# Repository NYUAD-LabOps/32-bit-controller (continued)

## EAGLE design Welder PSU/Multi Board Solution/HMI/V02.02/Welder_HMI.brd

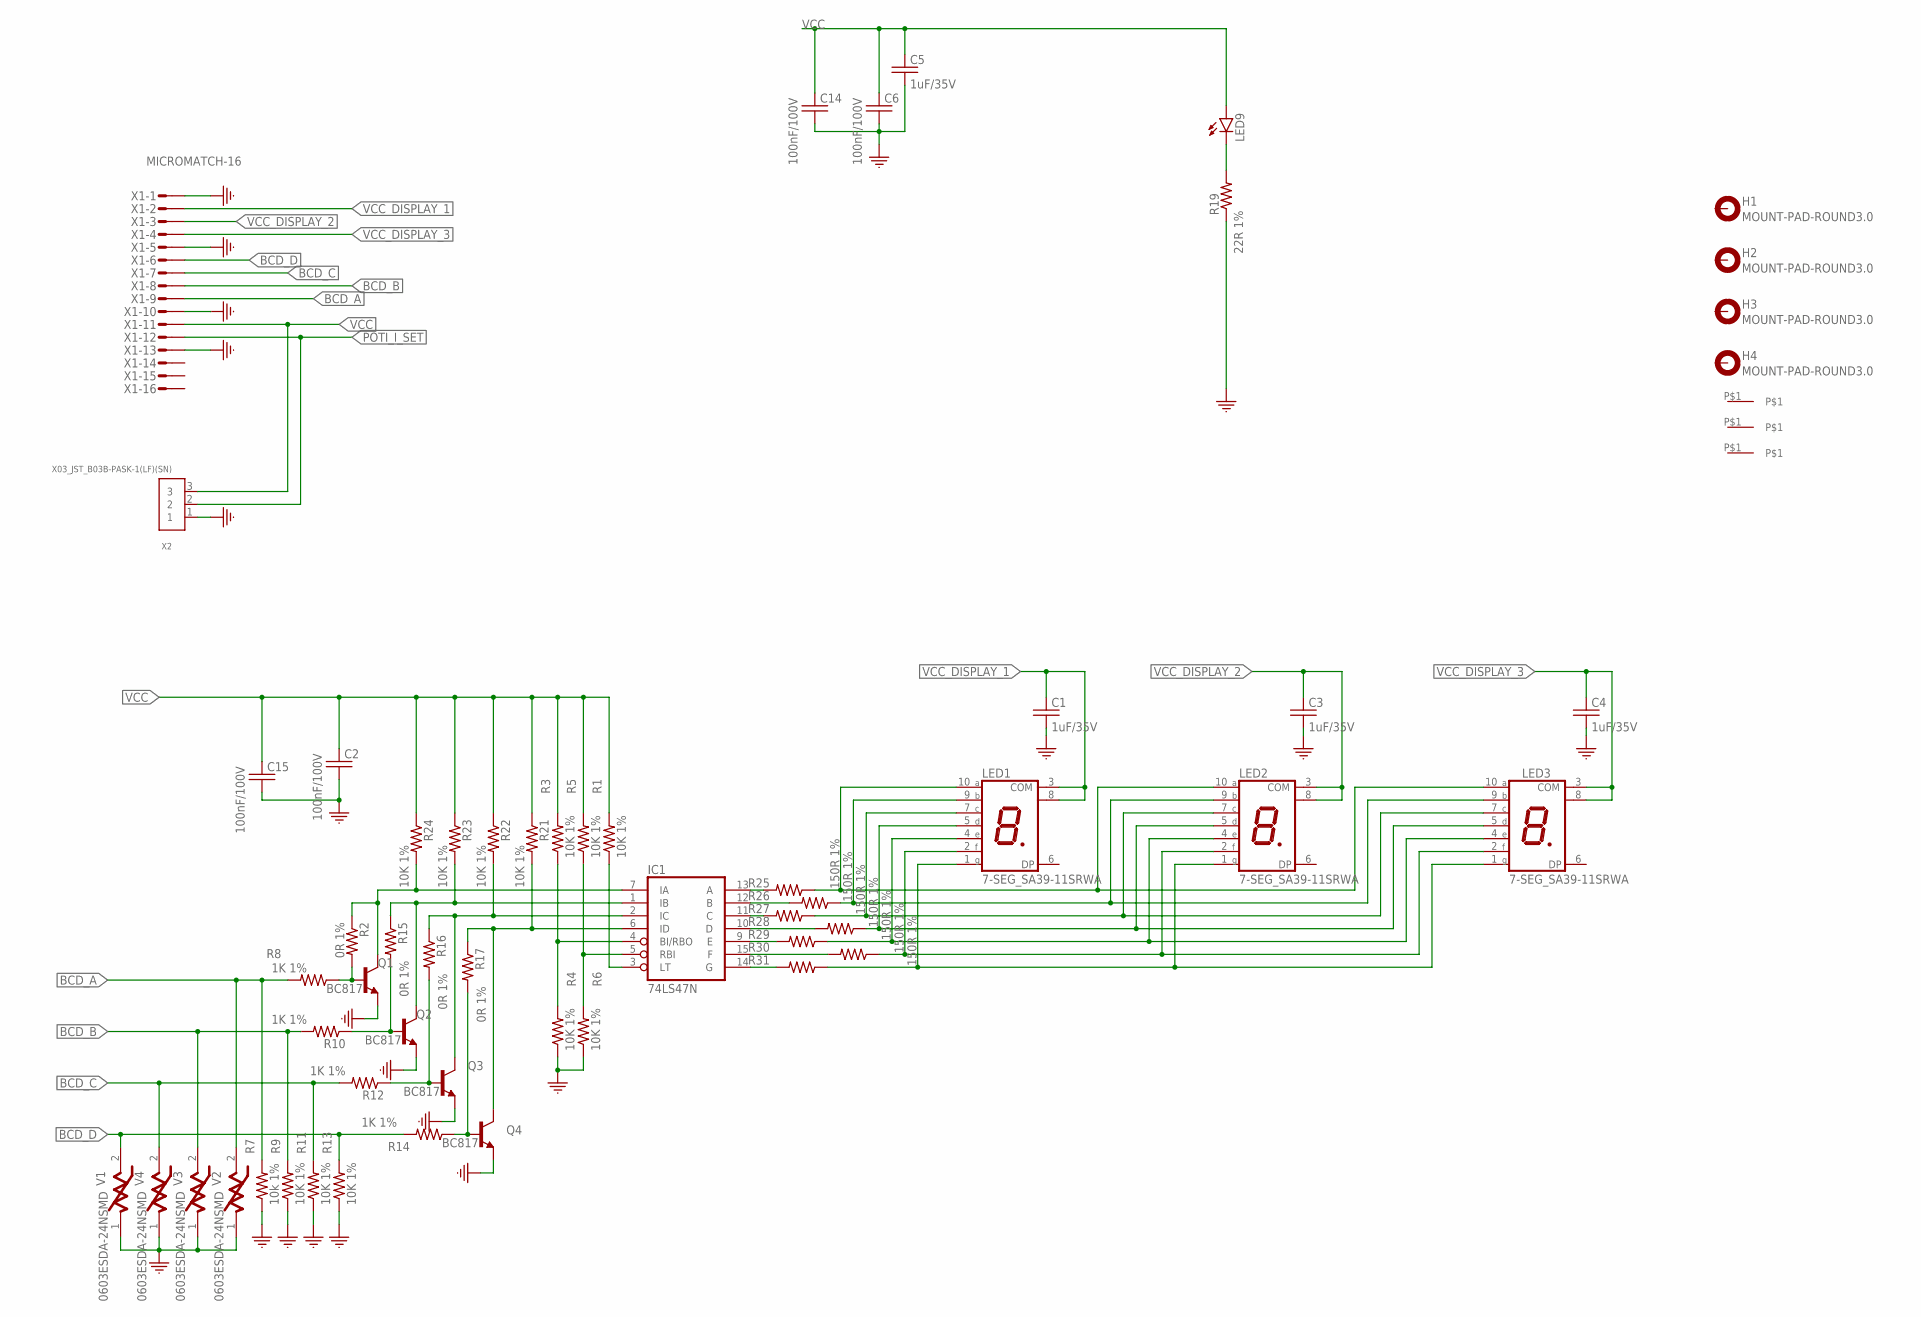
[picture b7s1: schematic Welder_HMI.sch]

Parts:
C1, C3, C4, C5: 1uF/35V; EIA0603
C2, C6, C14, C15: 100nF/100V; EIA0603
FID1, FID2, FID3: FIDUCIAL
H1, H2, H3, H4: MOUNT-PAD-ROUND3.0; 3,0-PAD
IC1: 74LS47N; DIL16
LED1, LED2, LED3: 7-SEG_SA39-11SRWA; SA39-11SRWA
LED9: LED5MM
Q1, Q2, Q3, Q4: BC817; SOT23
R1, R3, R4, R5, R6, R9, R11, R13, R21, R22, R23, R24: 10K 1%; EIA0603
R2, R15, R16, R17: 0R 1%; EIA0603
R7: 10k 1%; EIA0603
R8, R10, R12, R14: 1K 1%; EIA0603
R19: 22R 1%; EIA1206
R25, R26, R27, R28, R29, R30, R31: 150R 1%; EIA1206
V1, V2, V3, V4: 0603ESDA-24NSMD; EIA0603
X1: MICROMATCH-16
X2: X03_JST_B03B-PASK-1(LF)(SN)

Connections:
BCD_A: R7.2, R8.2, V2.2, X1.9
BCD_B: R9.2, R10.2, V3.2, X1.8
BCD_C: R11.2, R12.2, V4.2, X1.7
BCD_D: R13.2, R14.2, V1.2, X1.6
GND: C1.2, C2.2, C3.2, C4.2, C5.2, C6.2, C14.2, C15.2, IC1.8 (GND), Q1.2 (E), Q2.2 (E), Q3.2 (E), Q4.2 (E), R4.1, R6.1, R7.1, R9.1, R11.1, R13.1, R19.1, V1.1, V2.1, V3.1, V4.1, X1.1, X1.5, X1.10, X1.13, X2.1
unnamed: LED1.10 (A), LED2.10 (A), LED3.10 (A), R25.1
unnamed: LED1.9 (B), LED2.9 (B), LED3.9 (B), R26.1
unnamed: LED1.7 (C), LED2.7 (C), LED3.7 (C), R27.1
unnamed: LED1.5 (D), LED2.5 (D), LED3.5 (D), R28.1
unnamed: LED1.4 (E), LED2.4 (E), LED3.4 (E), R29.1
unnamed: LED1.2 (F), LED2.2 (F), LED3.2 (F), R30.1
unnamed: LED1.1 (G), LED2.1 (G), LED3.1 (G), R31.1
unnamed: IC1.4 (BI/RBO), R3.1, R4.2
unnamed: IC1.3 (LT), R1.1
unnamed: Q4.1 (B), R14.1, R17.2
unnamed: IC1.5 (RBI), R5.1, R6.2
unnamed: IC1.13 (A), R25.2
unnamed: Q3.1 (B), R12.1, R16.2
unnamed: Q2.1 (B), R10.1, R15.2
unnamed: Q1.1 (B), R2.2, R8.1
unnamed: IC1.7 (IA), Q1.3 (C), R2.1, R24.2
unnamed: IC1.1 (IB), Q2.3 (C), R15.1, R23.2
unnamed: IC1.2 (IC), Q3.3 (C), R16.1, R22.2
unnamed: IC1.6 (ID), Q4.3 (C), R17.1, R21.2
unnamed: LED9.K (C), R19.2
unnamed: IC1.12 (B), R26.2
unnamed: IC1.11 (C), R27.2
unnamed: IC1.10 (D), R28.2
unnamed: IC1.9 (E), R29.2
unnamed: IC1.15 (F), R30.2
unnamed: IC1.14 (G), R31.2
POTI_I_SET: X1.12, X2.2
VCC: C2.1, C5.1, C6.1, C14.1, C15.1, IC1.16 (VCC), LED9.A, R1.2, R3.2, R5.2, R21.1, R22.1, R23.1, R24.1, X1.11, X2.3
VCC_DISPLAY_1: C1.1, LED1.3 (COM), LED1.8 (COM), X1.2
VCC_DISPLAY_2: C3.1, LED2.3 (COM), LED2.8 (COM), X1.3
VCC_DISPLAY_3: C4.1, LED3.3 (COM), LED3.8 (COM), X1.4

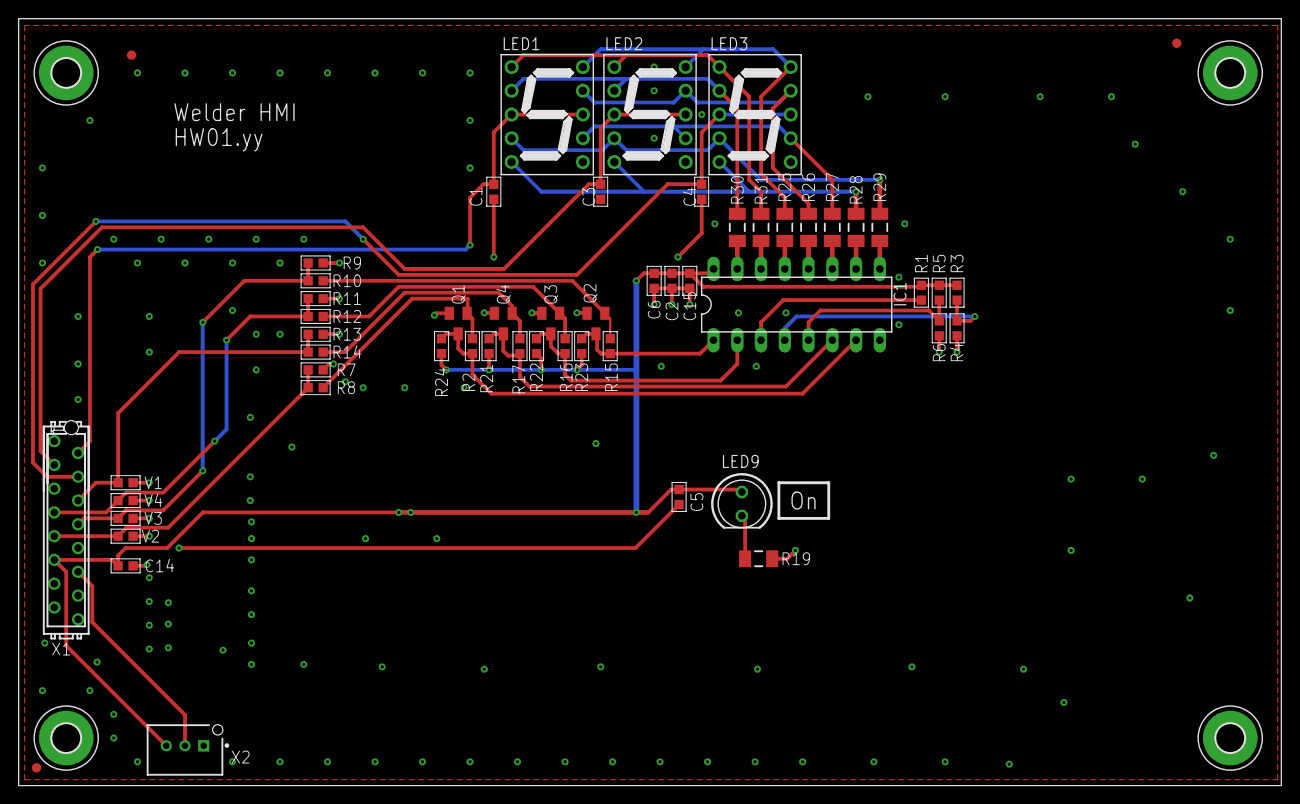
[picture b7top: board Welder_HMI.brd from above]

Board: 2 copper layers, 135.0 x 82.0 mm, 59 parts (0 on the bottom side), 36 nets.

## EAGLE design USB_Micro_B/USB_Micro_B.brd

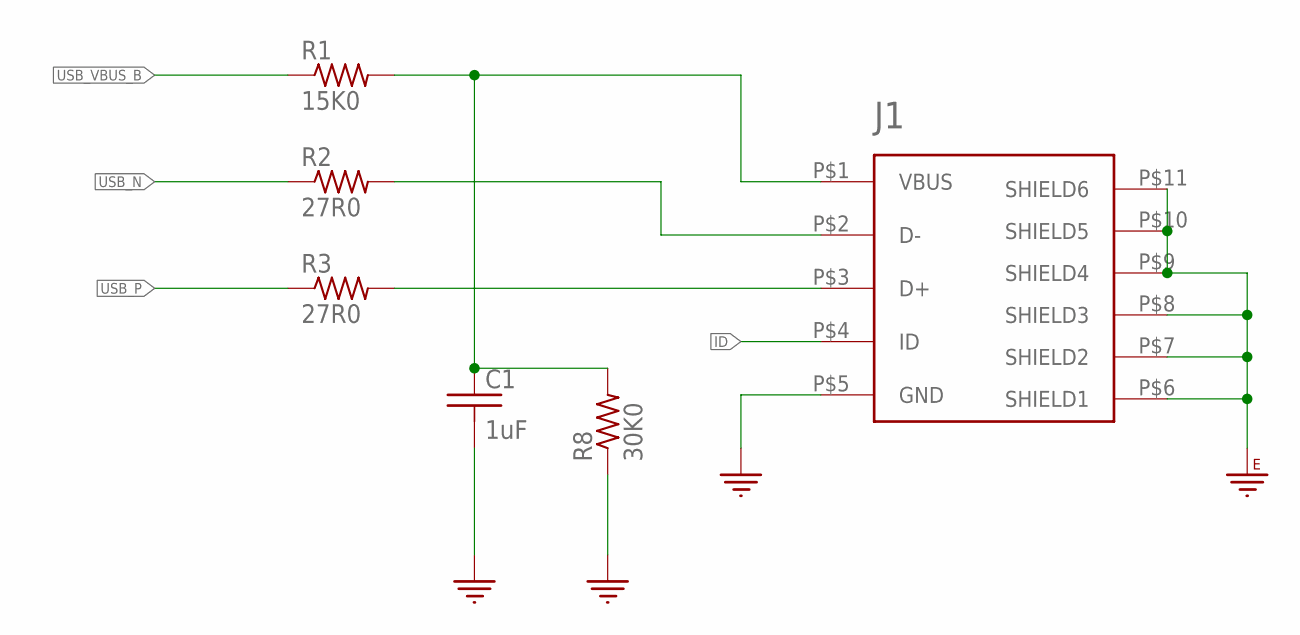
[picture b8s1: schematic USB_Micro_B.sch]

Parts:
C1: 1uF; 0402
J1: USB-B-Micro; USB_MICRO-B
R1: 15K0; 0402
R2, R3: 27R0; 0402
R8: 30K0; 0402

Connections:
D+1: J1.P$3 (D+), R3.2
D-1: J1.P$2 (D-), R2.2
GND: C1.2, J1.P$5 (GND), R8.1
GNDE: J1.P$6 (SHIELD1), J1.P$7 (SHIELD2), J1.P$8 (SHIELD3), J1.P$9 (SHIELD4), J1.P$10 (SHIELD5), J1.P$11 (SHIELD6)
ID: J1.P$4 (ID)
USB_N: R2.1
USB_P: R3.1
USB_VBUS_B: R1.1
VBUS1: C1.1, J1.P$1 (VBUS), R1.2, R8.2

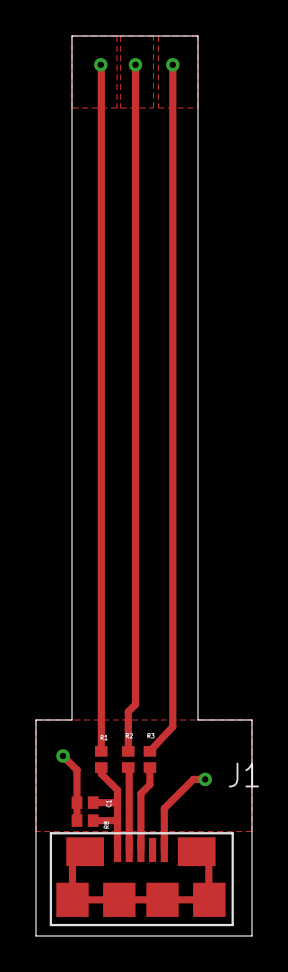
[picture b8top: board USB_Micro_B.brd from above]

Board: 2 copper layers, 12.0 x 50.0 mm, 6 parts (0 on the bottom side), 5 nets.

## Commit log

2020-11-05 Updated Parts
    Updated parts with manufacturer part numbers.
2020-11-05 Updated Board Parts
    Updated board parts to include PARTNO
2020-11-06 Updated board Design
2020-11-06 Updated Parts Numbers
2021-03-28 Updated Controller with fiducials
2021-04-09 Inverter Board
2021-04-24 Updated Inverter Schematic
2021-04-25 Updated inverter circuit to match updated library
2021-04-27 Updated v1p1 circuit.
2021-04-28 Updated Schematic
2021-04-28 Updated Inverter design.
2021-04-28 Updated to include correct diodes on power side of circuit.
2021-04-30 Updated Deko Schematic
2021-05-09 Update Welder PSU
    Added the Eagle Files..
    V00.00
    (Schematic and Layout Modifications Onegoing)
2021-05-09 V00.00 Changes
2021-05-09 V00.00 Changes
    Modified Refdes
2021-05-10 V00.00 Modifications
    Refdes of each Module has own offset
2021-05-11 V00.00 Changes
    Defined Layer Stackup, Net Classes, initial placement of Components "30_Mains_Input"
2021-05-11 V00.00
2021-05-12 HVDC Test Board
2021-05-12 Updated HVDC
2021-05-16 Updated Relay Control
2021-05-16 Updated controller
2021-05-16 V00.00 changes
    placing parts on PCB
2021-05-17 Updated board
2021-05-19 V00.00 changes
    Layout Ongoing
2021-05-19 V00.00
    PCB Layout Ongoing
2021-05-19 V00.00
    Changes Layout Ongoing
2021-05-22 Added new board
2021-05-22 V00.00 Changes
    Working on Layout
2021-05-23 Switched to RJ45 Connector
2021-05-23 Updated.
2021-05-23 V00.00
    Modifying Layout
2021-05-23 V00.00
    Layout Ongoing
2021-05-24 HW00.00
    Layout Changes finalization (No Galvanic isolation of I-V measurement of secondary)
2021-05-24 HW00.00
    Layout finishing touches
2021-05-25 HW00.00
    Layout finalization
2021-05-26 HW00.00
    Layout modifications
2021-05-26 Updated Callisto.
2021-05-26 HW00.00
    Drills of THT components under modification.. ongoing
2021-05-27 HW00.00
    Layout: Modified THT pads to match Labop drill bits
2021-05-27 Updated Callisto board.
2021-05-27 HW00.00
    Modified all THT Footprints to match Labops Drillbit set
2021-05-27 HW00.00
    Generated Production Files (Folder called Outputs)
2021-05-28 Updated Callisto boards.
2021-05-30 Updated boards
2021-05-31 Updated relay board.
2021-06-01 updated test boards
2021-06-01 Updated Callisto board
2021-06-02 Variant1 HW01.01
    Finished Updating to HW01.01.
    1st prototype will be Fabricated with this version
2021-06-09 Updated Callisto
2021-06-10 Added S3 Controller Board
2021-06-13 Added backplate
2021-06-16 Updated Renesas processor references.
2021-06-16 Added S3A6 board
2021-06-17 Updated controller design.
2021-06-18 board update
2021-07-26 40 Watt AC-DC Converter Module
    Input: Universal AC
    Output: 24V.12V.5V.3.3V
    Max Output Power = 40Watts.
    HW00.00 Prototype
2021-07-26 Update DESCRIPTION
2021-07-26 Added two Power Good LEDs
2021-08-02 HW02.02 Ongoing
    Schematic changes on HW01.01 under implementation
2021-08-05 HW02.02 Ongoing
    Variant with Synch Rectifiers
2021-08-09 HW02.02 Ongoing
    Finalizing schematic changes
2021-08-10 HW02.02 Ongoing
2021-09-05 Design Update
2021-09-06 HW01.01
    Based on TI Buck Regulator (TPS54202DDCR), Due to lack of availability of Buck used in HW00.00 (AP63301WU-7)
2021-09-06 HW02.02 Ongoing
    Placement and Routing finished. Final Tweaking of Layout still open (Solder Mask Opening, DRC Check, Mounting Holes, Milling between Transistor Pins)
2021-09-07 HW02.02
    Added Solder Mask Openings, and Milling slots between transistor pins.
2021-09-07 HW02.02
    Finalized - Via Stitching
2021-09-15 Updated Titan and Callisto
2021-10-07 HW02.02
    Added -5V Output and voltage regulator
2021-10-15 PNP Nozzle Setup NeoDen 4
2021-10-24 HW02.02 update
    Changed the Buck/Boost IC to Max764
2021-10-31 bom_Update
2021-11-08 PNP Update
2021-11-08 Updated PNP Files
2021-11-09 Updated Titan USB
2021-11-10 PNP CSV files Updated
2021-11-23 HW03.03 Modification
    Optimized voltage setting resistor values
2021-11-24 Schematic Changes Ongoing
    HW00.00
2021-11-24 HW01.01 Sch Changes
    Ongoing
2021-11-26 HW00.00 Ongoing
    Added PCB File
2021-11-28 HW00.00 Ongoing
    Schematic editing ongoing
2021-11-30 HW00.00 ongoing
    schematic changes ongoing
2021-11-30 HW03.03
    Corrected a resistor value in schematic
2022-02-15 Create .gitkeep
    This folder contains the files of the HW03.03 version of the Welder.
    These are Altium files, and PDF files of the schematic/Layout, in addition to the prduction files
2022-02-15 Create Production Files
2022-02-15 Create gitkeep
2022-02-15 Modificiation of Resistor values
    to Generate a 14V output instead of 12V
2022-03-08 HW00.00 Modifications
    Added FFC Connector (Schematic)
2022-03-08 HW00.00 modifications
    schematic MCU circuit
2022-03-08 HW00.00 modifications
2022-03-09 HW00.00 Modifications
    Schematic finalization
2022-03-09 HW00.00
    PCB Component placement ongoing
2022-03-10 HW00.00
    Component placement ongoing
2022-03-10 HW00.00
    Placement ongoing
2022-03-11 HW00.00 Ongoing
    Component placement ongoing
2022-03-11 HW00.00 Ongoing
    Placement Ongoing
2022-03-15 HW00.00 Ongoing
    Layout: component placement finalization..
2022-03-15 HW00.00 Ongoing
    LM317 added as voltage limiter in sch+.brd
2022-03-23 HW00.00
    Sch modification, new MCU + ESP32-Pico-Kit
2022-03-24 HW00.00 Sch Changes
    New MCU migration ongoing
2022-03-25 HW00.00 Update
    Layout placement finalization
2022-03-25 Revert "HW00.00 Update"
    This reverts commit 6a16d5ae0aeb23751d3b19f65fa50b6deefc484e.
2022-03-25 HW00.00 Placement Ongoing
2022-03-25 HW00.00 Ongoing
    Layout: Placement
2022-03-25 HW00.00 Ongoing
    Placement and Layout Ongoing
2022-03-27 HW00.00 Ongoing
    Layouting ongoing
2022-03-28 HW00.00 Layout Ongoing
2022-03-28 HW00.00 Onging
    Layout ongoing
2022-03-28 HW00.00 update
2022-03-28 HW00.00 Layout Ongoing
    Ongoing Changes On Layout
2022-03-28 HW00.00 ongoing
2022-03-29 HW00.00 Ongoing
    Layout ongoing
2022-03-29 HW00.00 Ongoing
    Layout Copper Pouring
2022-03-30 HW00.00 Ongoing
    Finalizing Layout
2022-03-30 Update Aqua_D_CTRL.brd
    Finalizing HW00.00 Layout
2022-03-30 HW00.00 Layout Finalization
    Adding stitching vias, silkscreen, etc..
2022-04-12 HW00.00 Ongoing
    Added an assembly variant Rseries between ESP32 5V supply pin and 5V0 Rail
2022-08-22 HW01.01
    Modified MCU Footprint.
    Copper below ESP32-Board Chip Antenna removed.
2022-08-22 Checking In the Gerber Files
    of HW00.00 and HW01.01
2022-09-05 Aqua D CTRL modification
    Changed the RJ45 connectors due to limited availability of previous one
2022-09-26 Teknic MSO
2022-09-28 Updated Teknic MSO
2022-09-29 HW01.01 Sch Change
    Resistor value changed
2022-09-29 Teknic X
2022-09-30 Updated DBs
2022-10-10 HW05.05 Import Ongoing
    Altium Project Import -> Eagle
2022-10-17 Update Callisto
2022-10-19 Updated MSO Teknic
2022-10-28 Added Output Indicator
2022-11-05 Updated Titan Design
2022-11-05 Updated Design added Output to 20 pin header
2022-11-07 Updated design
2022-11-08 Updated v1p00a
2022-11-10 HW05.05 Transfer to Eagle
    started copying schematic from Altium
2022-11-14 Updated ATX Breakout to 3oz copper.
2022-11-16 Updated Titan Servo
    Changed 2x10 header to 2-pin PicoBlade 53047 connectors for Thermistors
2022-11-16 Updated Titan Servo
2022-12-14 Added HMI PCB Folder
    Two folders: Controller and HMI
2022-12-14 PCB ongoing
2022-12-15 Finalizing HMI Board HW00.00
2022-12-19 Welder PSU HW05.05 Altium -> Eagle Ongoing
    Recreating schematic done, Netlisting Ongoing
2022-12-20 Archived Old Designs
2023-02-14 Updated Controller
    Updated controller. Added separate motor output control voltage and separate limit switch output voltage.
2023-03-27 Welder PSU HW05.05
    Translated to Eagle, Design Rule Check still open
2023-03-28 Welder PSU HW05.05
    Transferring into Eagle Done.
    Via Stitching, DRC still open
2023-04-11 Dosing Controller HMI HW01.01
    Minor Changes introduced.
2023-04-11 3xDosing Pumps Driver HW00.00
    For Capstone Project , Patrick Dowd.
2023-05-24 HW03.03 Ongoing
    Replacing AC/DC Module with Flyback Converter
2023-05-30 Oven_120V_Power_Breakout
2023-05-30 HW03.03
    Modified the AC/DC converter to a Flyback with custome transformer (Higher Power)
2023-06-01 HW02.02
    Improvements after HW Functional Testing
2023-06-01 HW03.03
    Done
2023-07-19 Updated test board
2023-07-20 HW00.00 Ready
    First Version Analog/ PWM LED Ring Dimmer
2023-07-20 HW03.03 Finished
    This Version switches to Flyback converter for the AC/DC Part
2023-07-28 HW modification Schematic + Layout
    SWDIO was connected to wrong pin, now modified
2023-08-04 Updated Titan to 6L
2023-08-04 LS Update.
2023-08-05 Updated motor IO board.
2023-08-06 Updated headers.
2023-08-10 HW01.01
    Fixed issue of not connected 24V0 Net, and added a DC Jack Connector , On Status LED, and Switch
2023-08-12 Updates.
2023-08-20 Updated 6Lv1p4
2023-08-21 6L Updated
2023-09-14 Arduino Shield
2023-11-21 Create Welder_Control (11-21-2023 10-20-10 AM).zip
    Packaged Project: Design Files + Output files (Gerbers, BOM, PDF, PnP)
2023-12-07 HW01.01 of Welder HMI
2024-02-29 modifications Aqua CTRL
2024-02-29 AC-DC Supply update
2024-02-29 HW00.00 Ongoing
    Sch changes
2024-02-29 LED Ring Driver HW01.01
2024-02-29 Organic Crystal Driver HW00.00
    Driver for Organic Crystal coated with magnetic Material.
2024-03-11 Create Main Board
2024-03-11 Adding Main Board Alium Packaged Files
2024-03-11 Moving the HW Design Files to HW Folder
2024-03-11 Create Welder_PSU_V01_22.zip
    Adding SW working version to Github: This version was tested successfully
2024-03-11 Changes on going
2024-04-25 HW01.01 Ongoing
    After Test Modifications..
2024-04-25 HW00.00
    Battery powered version... Initial Design
2024-05-06 HW00.00 Ongoing
    Added Coin battery and 32KHz Crystal for RTC retention
2024-05-06 HW01.01 changes
2024-09-03 HW01
    Layout Improvement of driving the 32KHz crystal resonator
2024-09-03 HW00
2024-09-03 HW00
    Oraibs Heatsink Test PCB
2024-09-03 HW01
